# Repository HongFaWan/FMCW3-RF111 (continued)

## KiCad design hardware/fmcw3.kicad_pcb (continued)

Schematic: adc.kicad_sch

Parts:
C19, C20, C217, C218, C222: 1u; SMD_0603
C22, C31, C216, C220: 2.2u; SMD_0603
C23, C24, C25, C27, C30, C219, C221, C223, C224, C225: 100n; SMD_0402
C163, C164, C165, C166, C167, C168: 100p; SMD_0402
C248: 22u; C0805_Murata_GRM21
C249: 47u; C1206_Murata_GRM31
C362: 2.2u; C0603_Assembly_Courtyard_ECO
C400, C401, C410, C412: 100n; SMD_0402; Tolerance 10%; Voltage 50V; MPN GRM155R71H104KE14D; LCSC C77020
C413: 100n; SMD_0402; Voltage 50V; Tolerance 10%; MPN GRM155R71H104KE14D; LCSC C77020
C806: 100n; SMD_0402; MPN GRM155R71H104KE14D
R20, R93: 0; SMD_0402
R21: 33; SMD_0402
R91: 4.7k; SMD_0402
R92: 10k; SMD_0402
R97, R98, R99, R100: 49.9; SMD_0402
R364, R422, R423: 30.9k; R0402_Yageo_Mount_V10; Tolerance 0.1%; MPN RT0402BRD0730K9L; LCSC C852715
R365: 499; R0402_Yageo_Mount_V10
R400, R401, R402, R403, R404, R405, R406, R407, R410, R411, R421, R424, R427, R429: 10k; R0402_Yageo_Mount_V10; Tolerance 0.1%; MPN RT0402BRD0710KL; LCSC C190095
R408, R409: 2.4k; R0402_Yageo_Mount_V10; Tolerance 1%; MPN RC0402FR-072K4L; LCSC C112296
R412: 4.99k; R0402_Yageo_Mount_V10; Tolerance 0.1%; MPN RT0402BRD074K99L; LCSC C852823
R420: 64.9k; R0402_Yageo_Mount_V10; Tolerance 0.1%; MPN RT0402BRD0764K9L; LCSC C852880
R425, R426: 31.6k; R0402_Panasonic_ERA2A_Mount_RF110; Tolerance 0.1%; MPN ERA-2ARB3162X; LCSC C2090771
R428: 100k; R0402_Yageo_Mount_V10; Tolerance 0.1%; MPN RT0402BRD07100KL; LCSC C852472
R431: 20.0k; R0402_Yageo_Mount_V10; Tolerance 0.1%; MPN RT0402BRD0720KL; LCSC C705630
R470: 10; R_0402_UniRoyal_Mount_V17_MFR; Tolerance 1%; MPN 0402WGF100JTCE; LCSC C25077
R807: 10.2k; R_0603_1608Metric; MPN ERA3ARW1022V
R808: 2.21M; R_0603_1608Metric; MPN RC0603FR-072M21L
U8: LTC2292; QFN-64-1EP_9x9mm_Pitch0.5mm
U39: LT3045EMSE#TRPBF; LT3045_MSE12_MFR
U400, U401: TMUX1511PWR; TSSOP-14_4.4x5mm_P0.65mm; MPN TMUX1511PWR; LCSC C2866750
U410: TPS386000RGPR; TPS386000_RGP20_EP2p15; MPN TPS386000RGPR; LCSC C702221
U412: SN74LVC1G17DBVR; SOT-23-5; MPN SN74LVC1G17DBVR; LCSC C7836
U413: SN74LVC1G07DBVR; SOT-23-5; MPN SN74LVC1G07DBVR; LCSC C7829
U806: TLV9021DCKR; SOT-353_SC-70-5; MPN TLV9021DCKR

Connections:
/3V3A: R406.1, R407.1, R425.1; also elsewhere on the board
/3V8: C248.1, U39.1 (IN), U39.2 (IN), U39.3 (IN), U39.4 (EN/UV), U39.7 (PGFB); also elsewhere on the board
/5V: R470.1; also elsewhere on the board
/ADC1+: R100.2; also elsewhere on the board
/ADC1-: R98.2; also elsewhere on the board
/ADC2+: R97.2; also elsewhere on the board
/ADC2-: R99.2; also elsewhere on the board
/ADC_CLK: U8.8 (CLKA), U8.9 (CLKB); also elsewhere on the board
/ADC_VCMA: R406.2, R408.2, R410.1; also elsewhere on the board
/ADC_VCMB: R407.2, R409.2, R411.1; also elsewhere on the board
/fpga/D0: U8.43 (DA0); also elsewhere on the board
/fpga/D1: U8.44 (DA1); also elsewhere on the board
/fpga/D2: U8.45 (DA2); also elsewhere on the board
/fpga/D3: U8.46 (DA3); also elsewhere on the board
/fpga/D4: U8.47 (DA4); also elsewhere on the board
/fpga/D5: U8.48 (DA5); also elsewhere on the board
/fpga/D6: U8.51 (DA6); also elsewhere on the board
/fpga/D7: U8.52 (DA7); also elsewhere on the board
/fpga/D8: U8.53 (DA8); also elsewhere on the board
/fpga/D9: U8.54 (DA9); also elsewhere on the board
/fpga/D10: U8.55 (DA10); also elsewhere on the board
/fpga/D11: U8.56 (DA11); also elsewhere on the board
/fpga/OFA: U8.57 (OFA); also elsewhere on the board
/fpga/OFB: U8.40 (OFB); also elsewhere on the board
/fpga/adc/ADn: C164.2, C165.1, R401.1, U8.2 (AINA-), U400.6 (D2)
/fpga/adc/ADp: C163.2, C164.1, R400.1, U8.1 (AINA+), U400.3 (D1)
/fpga/adc/ANALOG_RAILS_GOOD: R431.2, U410.15 (RESET1_N), U410.16 (RESET2_N), U410.17 (RESET3_N), U410.18 (RESET4_N), U412.2 (A), U806.1 (OUT)
/fpga/adc/ASn: R99.1, U400.5 (S2)
/fpga/adc/ASp: R97.1, U400.2 (S1)
/fpga/adc/BDn: C166.2, C167.1, R402.1, U8.15 (AINB-), U400.8 (D3)
/fpga/adc/BDp: C167.2, C168.1, R403.1, U8.16 (AINB+), U400.11 (D4)
/fpga/adc/BSn: R98.1, U400.9 (S3)
/fpga/adc/BSp: R100.1, U400.12 (S4)
/fpga/adc/GUARD5V_DAMPED: C400.1, C401.1, C410.1, R428.1, R431.1, R470.2, U400.14 (VDD), U401.14 (VDD), U410.1 (MR_N), U410.14 (VDD)
/fpga/adc/ILIM_U39: R365.1, U39.6 (ILIM)
/fpga/adc/MON_5V: R428.2, R429.1, U410.7 (SENSE4L)
/fpga/adc/MON_ADC: R423.2, R424.1, U410.9 (SENSE2)
/fpga/adc/MON_ADC_MID: R422.2, R423.1
/fpga/adc/MON_AMP: R426.2, R427.1, U410.8 (SENSE3)
/fpga/adc/MON_AMP_MID: R425.2, R426.1
/fpga/adc/MON_DIG: R420.2, R421.1, U410.10 (SENSE1)
/fpga/adc/REFHA: C217.1, C220.1, C221.1, U8.3 (REFHA), U8.4 (REFHA)
/fpga/adc/REFHB: C20.1, C22.2, C23.2, U8.13 (REFHB), U8.14 (REFHB)
/fpga/adc/REFLA: C218.1, C220.2, C221.2, U8.5 (REFLA), U8.6 (REFLA)
/fpga/adc/REFLB: C19.1, C22.1, C23.1, U8.11 (REFLB), U8.12 (REFLB)
/fpga/adc/SET_U39: C362.1, R364.1, U39.8 (SET)
/fpga/adc/VCMA_RAW: C216.1, C219.1, R404.1, U8.61 (VCMA), U401.2 (S1)
/fpga/adc/VCMA_SW: R408.1, U401.3 (D1)
/fpga/adc/VCMB_RAW: C30.1, C31.1, R405.1, U8.20 (VCMB), U401.5 (S2)
/fpga/adc/VCMB_SW: R409.1, U401.6 (D2)
ADC3V09: C24.1, C27.1, C222.1, C223.1, C224.1, C249.1, R20.2, R21.2, R91.1, R93.2, R422.1, U8.7 (VDD), U8.10 (VDD), U8.18 (VDD), U8.63 (VDD), U39.10 (OUTS), U39.11 (OUT), U39.12 (OUT); also elsewhere on the board
ADC_DB0: U8.26 (DB0); also elsewhere on the board
ADC_DB1: U8.27 (DB1); also elsewhere on the board
ADC_DB2: U8.28 (DB2); also elsewhere on the board
ADC_DB3: U8.29 (DB3); also elsewhere on the board
ADC_DB4: U8.30 (DB4); also elsewhere on the board
ADC_DB5: U8.33 (DB5); also elsewhere on the board
ADC_DB6: U8.34 (DB6); also elsewhere on the board
ADC_DB7: U8.35 (DB7); also elsewhere on the board
ADC_DB8: U8.36 (DB8); also elsewhere on the board
ADC_DB9: U8.37 (DB9); also elsewhere on the board
ADC_DB10: U8.38 (DB10); also elsewhere on the board
ADC_DB11: U8.39 (DB11); also elsewhere on the board
FMCW_RESET_N: U413.4 (Y); also elsewhere on the board
GND: C19.2, C20.2, C24.2, C25.2, C27.2, C30.2, C31.2, C163.1, C165.2, C166.1, C168.2, C216.2, C217.2, C218.2, C219.2, C222.2, C223.2, C224.2, C225.2, C248.2, C249.2, C362.2, C400.2, C401.2, C410.2, C412.2, C413.2, C806.2, R92.2, R364.2, R365.2, R400.2, R401.2, R402.2, R403.2, R404.2, R405.2, R410.2, R411.2, R412.2, R421.2, R424.2, R427.2, R429.2, R807.2, U8.17 (GND), U8.22 (SHDNB), U8.23 (~OEB), U8.31 (OGND), U8.50 (OGND), U8.58 (~OEA), U8.59 (SHDNA), U8.64 (GND), U8.65 (PAD), U39.9 (GND), U39.13 (GND), U400.7 (GND), U401.7 (GND), U401.8 (D3), U401.9 (S3), U401.10 (SEL3), U401.11 (D4), U401.12 (S4), U401.13 (SEL4), U410.6 (SENSE4H), U410.11 (NC_GND), U410.12 (GND), U410.20 (WDI), U410.21 (EP), U412.3 (GND), U413.3 (GND), U806.2 (V-); also elsewhere on the board
GUARD_ANALOG_EN: R412.1, R808.1, U400.1 (SEL1), U400.4 (SEL2), U400.10 (SEL3), U400.13 (SEL4), U401.1 (SEL1), U401.4 (SEL2), U412.4 (Y), U413.2 (A); also elsewhere on the board
GUARD_REF2V5: U806.4 (-); also elsewhere on the board
MIXER_UV_SENSE: R807.1, R808.2, U806.3 (+); also elsewhere on the board
unnamed: R91.2, R92.1, U8.60 (MODE)
unnamed: R21.1, U8.21 (MUX)
unnamed: R93.1, U8.62 (SENSEA)
unnamed: R20.1, U8.19 (SENSEB)

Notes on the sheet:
2/3 VDD clock duty stabilizer 2s complement signed output This helped for better waveform
Important Note: ECS-TXO-3225MV is pure sin. Adc does not like sin i guess. Other ref designed used clipped more square like sin. That is why clock stabilizer is needed.
U39: OUTS to COUT+; SET/CSET return to COUT-. 499R ILIM; PG/fast start unused.
ANALOG POWER-OFF ISOLATION - WORKING ECO, NOT FOR ORDER
4 IF legs + 2 VCM lines. Original ADC100pF and mandatory reference capacitors remain on ADCside.
GUARD_ANALOG_EN is driven by U410/U411/U412. Digital guards and PCB routing pending.
Guard supply damping: R470 10R / C25077 Only low-current ADC protection and monitor loads. RF power path remains on the original 5V rail.
Local mixer undervoltage interlock

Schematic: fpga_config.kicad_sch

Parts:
C18: 100n; SMD_0402
C170, C171, C187, C189, C190, C191, C192, C193, C197, C198, C199, C200, C201, C202, C203, C204, C250, C251: 470n; SMD_0402
C181: 100u; SMD_1210
C182, C184, C196: 47u; SMD_1206
C183, C185, C186, C188, C194, C195: 4.7u; SMD_0603
C252: 820p; SMD_0402; Manufacturer Part Number GRM1555C1H821GA01D
CON1: SD_Card_DM3BT; DM3BT-DSF-PEJS
D6: LED; Diode_0603
J2: Connector_02x08; PinHeader_2x8_P2.5mm
R10: DNP; SMD_0402; not fitted
R14, R112, R117: 4.7k; SMD_0402
R109: 1k; SMD_0402
R110, R114, R115: 0; SMD_0402
R118: 470; SMD_0402; Manufacturer Part Number RC0402FR-07470RL
R801, R802: 47k; R_0402_1005Metric; Manufacturer Part Number RC0402FR-0747KL
R803: 4.3; R_0402_1005Metric; Manufacturer Part Number RC0402FR-074R3L
SW1, SW2: B3U-1000P; B3U_1000P_MFR
U40: W25Q128JVPIQ; WSON-8_6x5mm_P1p27_W25Q128JVPIQ_WINDOWED; MPN W25Q128JVPIQ; LCSC C190862

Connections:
/1V0: C181.1, C183.1, C184.1, C186.1, C187.1, C189.1, C191.1, C250.1; also elsewhere on the board
/1V8: C182.1, C185.1, C188.1, C190.1, C192.1, C193.1; also elsewhere on the board
/fpga/CARD_DETECT: CON1.9 (CARD_DETECT1); also elsewhere on the board
/fpga/INIT_B: R117.2; also elsewhere on the board
/fpga/M0: R110.2; also elsewhere on the board
/fpga/M1: R114.1; also elsewhere on the board
/fpga/M2: R10.1, R115.1; also elsewhere on the board
/fpga/PIN7: J2.6; also elsewhere on the board
/fpga/PIN8: J2.4; also elsewhere on the board
/fpga/PIN10: J2.5; also elsewhere on the board
/fpga/PIN11: J2.3; also elsewhere on the board
/fpga/PIN12: J2.1; also elsewhere on the board
/fpga/PROG_B: R112.2, SW2.1; also elsewhere on the board
/fpga/SD_CLK: CON1.5 (CLK); also elsewhere on the board
/fpga/SD_CMD: CON1.3 (CMD); also elsewhere on the board
/fpga/SD_DAT0: CON1.7 (DAT0); also elsewhere on the board
/fpga/SD_DAT1: CON1.8 (DAT1); also elsewhere on the board
/fpga/SD_DAT2: CON1.1 (DAT2); also elsewhere on the board
/fpga/SD_DAT3: CON1.2 (CD/DAT3); also elsewhere on the board
/fpga/SPI_CLK: U40.6 (CLK); also elsewhere on the board
/fpga/SPI_CS: R118.2, U40.1 (~CS); also elsewhere on the board
/fpga/SPI_MISO: U40.2 (DO(IO1)); also elsewhere on the board
/fpga/SPI_MOSI: U40.5 (DI(IO0)); also elsewhere on the board
/fpga/USER_LED: R109.1; also elsewhere on the board
/fpga/fpga_config/FLASH_VCC: C252.1, R801.1, R802.2, R803.2, U40.8 (VCC)
FMCW_RESET_N: R14.2, SW1.1; also elsewhere on the board
GND: C18.2, C170.2, C171.2, C181.2, C182.2, C183.2, C184.2, C185.2, C186.2, C187.2, C188.2, C189.2, C190.2, C191.2, C192.2, C193.2, C194.2, C195.2, C196.2, C197.2, C198.2, C199.2, C200.2, C201.2, C202.2, C203.2, C204.2, C250.2, C251.2, C252.2, CON1.6 (VSS), CON1.10 (CARD_DETECT2), CON1.11 (SHELL), D6.1 (K), J2.14, J2.16, R114.2, R115.2, SW1.2, SW2.2, U40.4 (GND), U40.9 (EP); also elsewhere on the board
LO_ADC_CONV_REQ_N: J2.7; also elsewhere on the board
LO_ADC_CS_N: J2.9; also elsewhere on the board
LO_ADC_SCK: J2.8; also elsewhere on the board
LO_ADC_SDO: J2.10; also elsewhere on the board
LO_DSA_LE: J2.2; also elsewhere on the board
unnamed: D6.2 (A), R109.2
unnamed: R802.1, U40.7 (~HOLD(IO3))
unnamed: R801.2, U40.3 (~WP(IO2))
PA_ARM_PULSE: J2.11; also elsewhere on the board
PA_INTERLOCK_N: J2.12; also elsewhere on the board

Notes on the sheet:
VCCBRAM
in SPI Flash mode, JTAG can be used.
VCCINT
32 is not supported by vivado openFPGALoader is needed. 128 is same price supported and more memory is available.
VCCAUX
VCCO_0
Mode M[2:0] Master SPI 001 JTAG 101
VCCO

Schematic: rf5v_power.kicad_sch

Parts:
C657: 2.2uF effective at DC, ≥50V; C_1210_3225Metric; Manufacturer Part Number C1210C106K5RAC7800
C658: 100nF ≥50V; C_0603_1608Metric; Manufacturer Part Number C0603C104K5RACTU
C659: 1uF; C_0603_1608Metric; Manufacturer Part Number C0603C105K4RACTU
C660, C661, C662: C3225X7R1E226M250AB; C_1210_3225Metric; Manufacturer Part Number C3225X7R1E226M250AB
C663, C665, C666: C2012X5R1E226M125AC; C_0805_2012Metric; Manufacturer Part Number C2012X5R1E226M125AC
C664: 470nF ≥16V; C_0603_1608Metric; Manufacturer Part Number C0603C474K4RACTU
R661: 47.5k, 0.1%; R_0402_1005Metric; Manufacturer Part Number RT0402BRD0747K5L
R662: 10k, 0.1%; R_0402_1005Metric; Manufacturer Part Number RT0402BRD0710KL
R664: 49.9k, 0.1%; R_0402_1005Metric; Manufacturer Part Number RT0402BRD0749K9L
U657: TPSM365R6FRDNR; TPSM365R6_RDN0011A_TI_4mil; Manufacturer Part Number TPSM365R6FRDNR
U658: LT3045EMSE#TRPBF; LT3045_MSE12_MFR; Manufacturer Part Number LT3045EMSE#TRPBF

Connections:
/power/12V: C657.1, C658.1, U657.2 (EN), U657.3 (VIN); also elsewhere on the board
/power/RF5V power/LO_BUCK_FB: R661.2, R662.1, U657.9 (FB)
/power/RF5V power/LO_BUCK_VCC: C659.1, U657.8 (VCC), U657.11 (RT)
/power/RF5V power/LO_LDO_SET: C664.1, R664.1, U658.8 (SET)
GND: C657.2, C658.2, C659.2, C660.2, C661.2, C662.2, C663.2, C664.2, C665.2, C666.2, R662.2, R664.2, U657.10 (PGND), U658.6 (ILIM), U658.9 (GND), U658.13 (EP); also elsewhere on the board
LO5V75: C660.1, C661.1, C662.1, C663.1, R661.1, U657.4 (VOUT), U658.1 (IN1), U658.2 (IN2), U658.3 (IN3), U658.4 (EN/UV), U658.7 (PGFB); also elsewhere on the board
RF5V_NEW: C665.1, C666.1, U658.10 (OUTS), U658.11 (OUT1), U658.12 (OUT2); also elsewhere on the board

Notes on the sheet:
Independent LO power supply

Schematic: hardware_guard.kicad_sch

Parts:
C650, C651, C652, C653, C654, C655, C656: 100nF; C_0402_1005Metric; Manufacturer Part Number GRM155R71H104KE14D
C670, C671, C673, C674: 100n; C_0402_1005Metric; Manufacturer Part Number GRM155R71H104KE14D
C672: 1u; C_0603_1608Metric; Manufacturer Part Number C0603C105K4RACTU
Q650: MMBT3904LT1G; SOT-23; Manufacturer Part Number MMBT3904LT1G
Q651: AO3400A; SOT-23; Manufacturer Part Number AO3400A
R650: 73.2k, 0.1%,25ppm; R_0402_1005Metric; Manufacturer Part Number RT0402BRD0773K2L
R651, R653: 10k, 0.1%,25ppm; R_0402_1005Metric; Manufacturer Part Number RT0402BRD0710KL
R652: 110k, 0.1%,25ppm; R_0402_1005Metric; Manufacturer Part Number RT0402BRD07110KL
R654, R655, R656, R657, R679, R680: 47k; R_0402_1005Metric; Manufacturer Part Number RC0402FR-0747KL
R658: 1.50k; R_0402_1005Metric; Manufacturer Part Number RC0402FR-071K5L
R659: 68; R_0402_1005Metric; Manufacturer Part Number RC0402FR-0768RL
R660, R674, R678: 4.7k; R_0402_1005Metric; Manufacturer Part Number RC0402FR-074K7L
R670: 2.00k 0.1% 25ppm; R_0402_1005Metric; Manufacturer Part Number RT0402BRD072KL
R671: 2.15k 0.1% 25ppm; R_0402_1005Metric; Manufacturer Part Number RT0402BRD072K15L
R672: 24 1% 100ppm; R_0402_1005Metric; Manufacturer Part Number RC0402FR-0724RL
R673: 560k 1% 100ppm; R_0402_1005Metric; Manufacturer Part Number RC0402FR-07560KL
R675: 13.0k 0.1% 25ppm; R_0402_1005Metric; Manufacturer Part Number RT0402BRD0713KL
R676: 11.0k 0.1% 25ppm; R_0402_1005Metric; Manufacturer Part Number RT0402BRD0711KL
R677: 3.3M; R_0402_1005Metric; Manufacturer Part Number RC0402FR-073M3L
U650, U651: TLV3012BIDBVR; SOT-23-6; Manufacturer Part Number TLV3012BIDBVR
U652: SN74LVC2G08DCUR; VSSOP-8_2.3x2mm_P0.5mm; Manufacturer Part Number SN74LVC2G08DCUR
U653: SN74LVC2G07DCKR; SOT-363_SC-70-6; Manufacturer Part Number SN74LVC2G07DCKR
U654, U655: SN74LVC1G11DCKR; SOT-363_SC-70-6; Manufacturer Part Number SN74LVC1G11DCKR
U656: SN74LVC1G74DCUR; VSSOP-8_2.3x2mm_P0.5mm; Manufacturer Part Number SN74LVC1G74DCUR
U667: TLV9022DDFR; SOT-23-8; Manufacturer Part Number TLV9022DDFR
U668: REF3425IDBVR; SOT-23-6; Manufacturer Part Number REF3425IDBVR
U669: SN74LVC1G11DBVR; SOT-23-6; Manufacturer Part Number SN74LVC1G11DBVR
U670: SN74LVC1G97DBVR; SOT-23-6; Manufacturer Part Number SN74LVC1G97DBVR

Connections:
/power/Rail interlock/ARM_Q: U652.6 (2B), U656.5 (Q)
/power/Rail interlock/GUARD_ARMED: U652.3 (2Y), U655.3 (B)
/power/Rail interlock/LO5V75_OK: R677.1, R678.2, U667.7 (PRE_OD), U669.6 (C)
/power/Rail interlock/LO5V75_UV_SENSE: R675.2, R676.1, R677.2, U667.5 (IN2+)
/power/Rail interlock/OV_REF: U651.3 (IN+), U651.5 (REF)
/power/Rail interlock/PA_KILL_BASE: Q650.1 (B), Q651.3 (D), R658.2
/power/Rail interlock/PA_KILL_RELEASE: Q651.1 (G), R659.2, R660.1
/power/Rail interlock/PA_LATCH_CLR_N: U654.4 (Y), U656.6 (NCLR)
/power/Rail interlock/RAW_OV_OK: U651.1 (OUT), U652.2 (1B)
/power/Rail interlock/RAW_OV_SENSE: R652.2, R653.1, U651.4 (IN-)
/power/Rail interlock/RAW_UV_OK: U650.1 (OUT), U652.1 (1A)
/power/Rail interlock/RAW_UV_SENSE: R650.2, R651.1, U650.3 (IN+)
/power/Rail interlock/RF5_LEVEL_OK: R673.1, R674.2, U667.1 (RF5_OD), U669.3 (B)
/power/Rail interlock/RF5_UV_LOW: R671.2, R672.1
/power/Rail interlock/RF5_UV_SENSE: R670.2, R671.1, R673.2, U667.3 (IN1+)
/power/Rail interlock/UV_REF: U650.4 (IN-), U650.5 (REF)
FMCW_RESET_N: U653.6 (1Y_OD), U654.3 (B); also elsewhere on the board
FTDI_RESET_N: U653.4 (2Y_OD); also elsewhere on the board
GND: C650.2, C651.2, C652.2, C653.2, C654.2, C655.2, C656.2, C670.2, C671.2, C672.2, C673.2, C674.2, Q650.2 (E), Q651.2 (S), R651.2, R653.2, R654.2, R655.2, R656.2, R657.2, R660.2, R672.2, R676.2, R679.2, U650.2 (V-), U651.2 (V-), U652.4 (GND), U653.2 (GND), U654.2 (GND), U655.2 (GND), U656.4 (GND), U667.4 (GND), U668.1 (GND), U668.2 (GND), U669.2 (GND), U670.2 (GND); also elsewhere on the board
GUARD_ANALOG_EN: U652.5 (2A); also elsewhere on the board
GUARD_EXISTING_RF_OK: U669.4 (Y); also elsewhere on the board
GUARD_RAW_OK: R654.1, U652.7 (1Y), U669.1 (A); also elsewhere on the board
GUARD_REF2V5: C672.1, U667.2 (IN1-), U667.6 (IN2-), U668.5 (OUT_S), U668.6 (REF); also elsewhere on the board
GUARD_RF_READY: R679.1, U653.1 (1A), U654.1 (A), U655.1 (A), U670.6 (SEL); also elsewhere on the board
GUARD_USB_READY: U653.3 (2A); also elsewhere on the board
LO5V75: R675.1; also elsewhere on the board
LO_ADC_CONV: U670.4 (Y); also elsewhere on the board
LO_ADC_CONV_REQ_N: R680.2, U670.3 (DATA_VALID); also elsewhere on the board
PA_ARM_PULSE: R655.1, U656.1 (CLK); also elsewhere on the board
PA_EN_G: Q650.3 (C); also elsewhere on the board
PA_INTERLOCK_N: R656.1, U654.6 (C), U655.6 (C); also elsewhere on the board
PA_OE_HW: R657.1, R659.1, U655.4 (Y); also elsewhere on the board
PA_VCC1: R658.1; also elsewhere on the board
RF5V_NEW: R670.1; also elsewhere on the board
VIN_RAW_12V: R650.1, R652.1; also elsewhere on the board

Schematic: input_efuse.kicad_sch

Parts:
C680: 100nF 100V; C_0805_2012Metric
C681: 2.2uF 100V X7R; C_1210_3225Metric
C682: 22nF 50V; C_0603_1608Metric
C683: EEH-ZK1V101XP; CP_Elec_6.3x7.7
R780: 64.9k 0.1%; R_0603_1608Metric
R781, R783: 10.0k 0.1%; R_0603_1608Metric
R782: 121k 0.1%; R_0603_1608Metric
R784: 5.49k 0.1%; R_0603_1608Metric
R785: 1.2R pulse rated; R_1210_3225Metric
U680: TPS26600PWPR; HTSSOP-16-1EP_4.4x5mm_P0.65mm_EP3.4x5mm_Mask2.66x2.46mm

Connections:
/power/12V: C683.1; also elsewhere on the board
/power/Input eFuse/DAMP: C681.1, R785.2
/power/Input eFuse/DVDT: C682.1, U680.12 (dVdT)
/power/Input eFuse/EFUSE_RTN: C682.2, R781.2, R783.2, R784.2, U680.6 (MODE), U680.8 (RTN), U680.17 (RTN)
/power/Input eFuse/ILIM: R784.1, U680.11 (ILIM)
/power/Input eFuse/OV: R782.2, R783.1, U680.5 (OVP)
/power/Input eFuse/UV: R780.2, R781.1, U680.3 (UVLO)
EFUSE_OUT_12V: U680.15 (OUT), U680.16 (OUT); also elsewhere on the board
GND: C680.2, C681.2, C683.2, U680.9 (GND); also elsewhere on the board
VIN_RAW_12V: C680.1, R780.1, R782.1, R785.1, U680.1 (IN), U680.2 (IN); also elsewhere on the board

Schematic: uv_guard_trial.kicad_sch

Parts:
C790, C791, C792, C793: 100n; C_0402_1005Metric; Manufacturer Part Number GRM155R71H104KE14D
C794: 33p C0G; C_0402_1005Metric; Manufacturer Part Number CC0402FRNPO9BN330
R790: 4.30k 0.05% 10ppm; R_0402_1005Metric; Manufacturer Part Number ERA2VRW4301X
R791: 1.50k 0.05% 10ppm; R_0402_1005Metric; Manufacturer Part Number ERA2VRW1501X
R792: 2.61k 0.1% 10ppm; R_0402_1005Metric; Manufacturer Part Number ERA-2ARB2611X
R793: 10.0k 0.1% 10ppm; R_0402_1005Metric; Manufacturer Part Number ERA-2ARB103X
R794, R795: 4.7k; R_0402_1005Metric; Manufacturer Part Number RC0402FR-074K7L
R796: 10k; R_0402_1005Metric; Manufacturer Part Number RC0402FR-0710KL
R797: 47k; R_0402_1005Metric; Manufacturer Part Number RC0402FR-0747KL
U685: TLV9022DDFR; SOT-23-8; Manufacturer Part Number TLV9022DDFR
U686, U687: SN74LVC1G11DCKR; SOT-363_SC-70-6; Manufacturer Part Number SN74LVC1G11DCKR
U688: TPS3808G33DBVR; SOT-23-6; Manufacturer Part Number TPS3808G33DBVR

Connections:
/power/Tune and IO protection/IO_FAST_OK: R795.2, U685.7 (IO_OD), U687.3 (B), U688.3 (MR)
/power/Tune and IO protection/IO_STARTUP_OK: R796.2, U687.6 (C), U688.1 (RESET_OD)
/power/Tune and IO protection/IO_UV_SENSE: R792.2, R793.1, U685.5 (IN2+)
/power/Tune and IO protection/TUNE_OK: R794.2, U685.1 (TUNE_OD), U686.3 (B)
/power/Tune and IO protection/TUNE_UV_SENSE: C794.1, R790.2, R791.1, U685.3 (IN1+)
GND: C790.2, C791.2, C792.2, C793.2, C794.2, R791.2, R793.2, R797.2, U685.4 (GND), U686.2 (GND), U687.2 (GND), U688.2 (GND); also elsewhere on the board
GUARD_EXISTING_RF_OK: U686.1 (A); also elsewhere on the board
GUARD_RAW_OK: U687.1 (A); also elsewhere on the board
GUARD_REF2V5: U685.2 (IN1-), U685.6 (IN2-); also elsewhere on the board
GUARD_RF_READY: U686.4 (Y); also elsewhere on the board
GUARD_USB_READY: R797.1, U686.6 (C), U687.4 (Y); also elsewhere on the board
TUNE_10V: R790.1; also elsewhere on the board

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
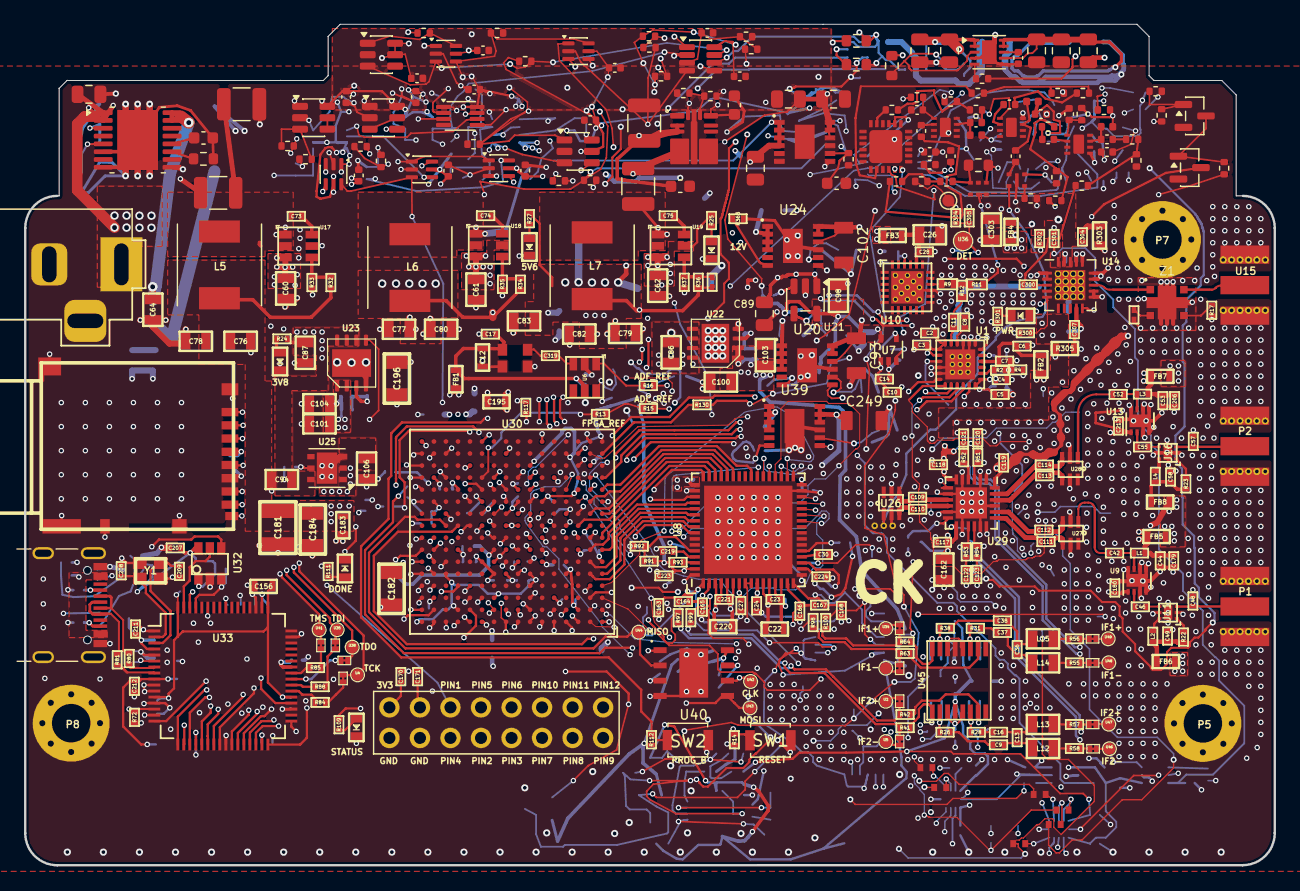
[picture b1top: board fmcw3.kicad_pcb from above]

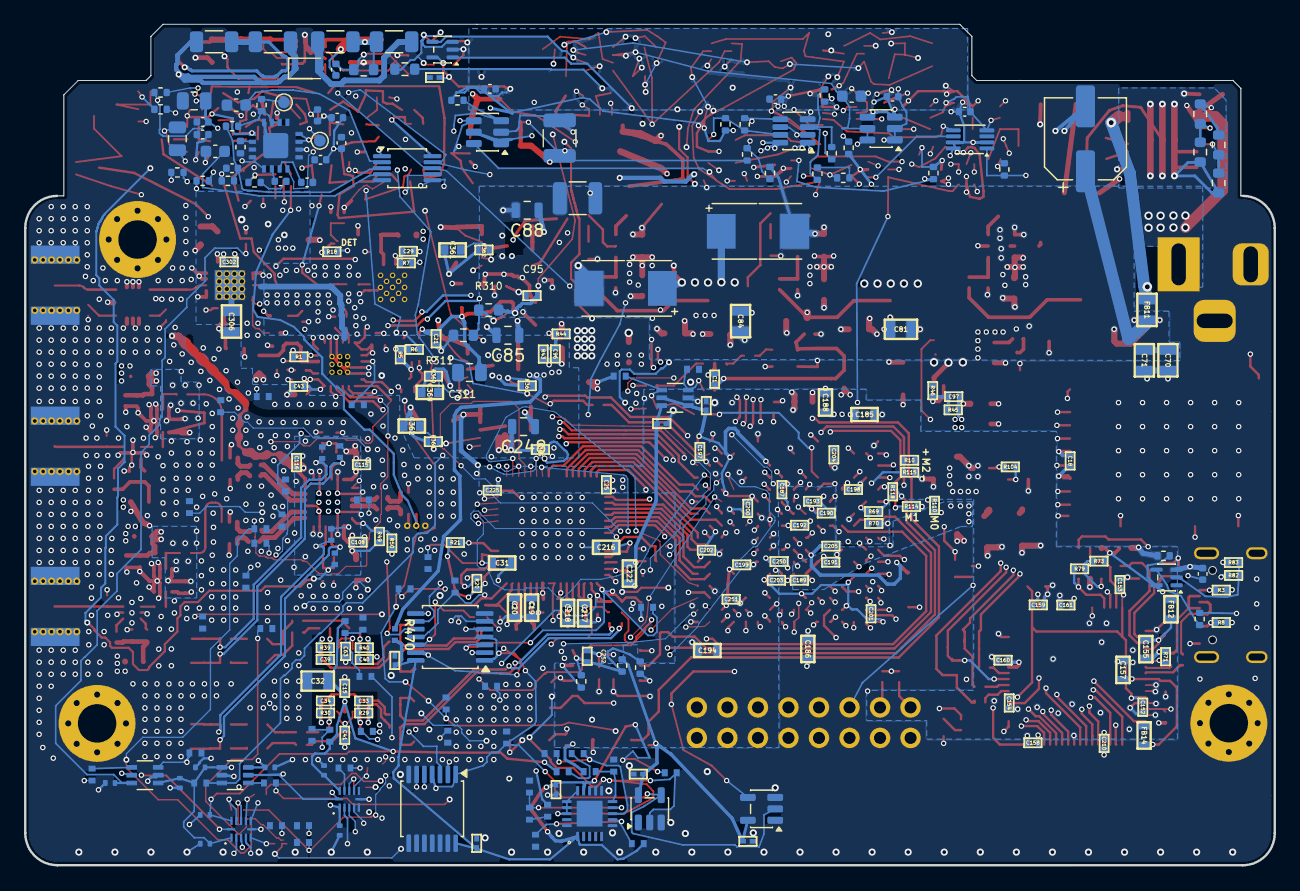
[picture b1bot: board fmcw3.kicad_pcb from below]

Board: 6 copper layers, 104.0 x 70.0 mm, 662 parts (265 on the bottom side), 393 nets.

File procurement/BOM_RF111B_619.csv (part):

位号,单片实装净数,面,原理图标值,工程封装,设计订货号,制造商,型号选择记录,工程及来料要求,核对链接
C1,1,底,100n,Footprints:SMD_0402,GRM155R71H104KE14D,Murata,工程原指定,Tolerance: 10%; Voltage: 50V,
C2,1,顶,100n,Footprints:SMD_0402,GRM155R71H104KE14D,Murata,工程原指定,Tolerance: 10%; Voltage: 50V,
C3,1,顶,10p,Footprints:SMD_0402,GRM1555C1H100GA01D,muRata,工程原指定,,
C4,1,顶,100n,Footprints:SMD_0402,GRM155R71H104KE14D,Murata,工程原指定,Tolerance: 10%; Voltage: 50V,
C5,1,顶,10p,Footprints:SMD_0402,GRM1555C1H100GA01D,muRata,工程原指定,,
C6,1,顶,100n,Footprints:SMD_0402,GRM155R71H104KE14D,Murata,工程原指定,Tolerance: 10%; Voltage: 50V,
C7,1,顶,10p,Footprints:SMD_0402,GRM1555C1H100GA01D,muRata,工程原指定,,
C8,1,顶,10p,Footprints:SMD_0402,GRM1555C1H100GA01D,muRata,工程原指定,,
C9,1,顶,10n,Footprints:SMD_0402,GRM1555C1E103GE01D,Murata,工程原指定,,
C10,1,顶,6.8n,Footprints:SMD_0402,GRM1555C1H682GE01D,muRata,工程原指定,,
C11,1,顶,10p,Footprints:SMD_0402,GRM1555C1H100GA01D,muRata,工程原指定,,
C12,1,顶,1u,Footprints:SMD_0603,GRM188R61E105KA12D,muRata,工程原指定,,
C13,1,顶,2.2n,Footprints:SMD_0402,GRM1555C1H222GA01D,muRata,工程原指定,,
C14,1,顶,68p,Footprints:SMD_0402,GRM1555C1H680GA01D,muRata,工程原指定,,
C15,1,底,100n,Footprints:SMD_0402,GRM155R71H104KE14D,Murata,工程原指定,Tolerance: 10%; Voltage: 50V,
C16,1,顶,10n,Footprints:SMD_0402,GRM1555C1E103GE01D,Murata,工程原指定,,
C17,1,顶,100n,Footprints:SMD_0402,GRM155R71H104KE14D,Murata,工程原指定,Tolerance: 10%; Voltage: 50V,
C18,1,底,100n,Footprints:SMD_0402,GRM155R71H104KE14D,Murata,工程原指定,Tolerance: 10%; Voltage: 50V,
C19,1,底,1u,Footprints:SMD_0603,GRM188R61E105KA12D,muRata,工程原指定,,
C20,1,底,1u,Footprints:SMD_0603,GRM188R61E105KA12D,muRata,工程原指定,,
C21,1,底,100n,Footprints:SMD_0402,GRM155R71H104KE14D,Murata,工程原指定,Tolerance: 10%; Voltage: 50V,
C22,1,顶,2.2u,Footprints:SMD_0603,GRM188R61A225KE34D,muRata,工程原指定,,
C23,1,顶,100n,Footprints:SMD_0402,GRM155R71H104KE14D,Murata,工程原指定,Tolerance: 10%; Voltage: 50V,
C24,1,顶,100n,Footprints:SMD_0402,GRM155R71H104KE14D,Murata,工程原指定,Tolerance: 10%; Voltage: 50V,
C25,1,底,100n,Footprints:SMD_0402,GRM155R71H104KE14D,Murata,工程原指定,Tolerance: 10%; Voltage: 50V,
C26,1,顶,10u,Footprints:SMD_0805,GRM21BR61E106KA73L,muRata,工程原指定,,
C27,1,顶,100n,Footprints:SMD_0402,GRM155R71H104KE14D,Murata,工程原指定,Tolerance: 10%; Voltage: 50V,
C28,1,顶,10n,Footprints:SMD_0402,GRM1555C1E103GE01D,Murata,工程原指定,,
C30,1,顶,100n,Footprints:SMD_0402,GRM155R71H104KE14D,Murata,工程原指定,Tolerance: 10%; Voltage: 50V,
C31,1,底,2.2u,Footprints:SMD_0603,GRM188R61A225KE34D,muRata,工程原指定,,
C33,1,底,5p,Footprints:SMD_0402,GRM1555C1H5R0BA01D,muRata,工程原指定,,
C34,1,底,5p,Footprints:SMD_0402,GRM1555C1H5R0BA01D,muRata,工程原指定,,
C36,1,顶,2.2n,Footprints:SMD_0402,GRM1555C1H222GA01D,muRata,工程原指定,,
C37,1,顶,10n,Footprints:SMD_0402,GRM1555C1E103GE01D,Murata,工程原指定,,
C38,1,顶,10n,Footprints:SMD_0402,GRM1555C1E103GE01D,Murata,工程原指定,,
C39,1,底,5p,Footprints:SMD_0402,GRM1555C1H5R0BA01D,muRata,工程原指定,,
C40,1,底,5p,Footprints:SMD_0402,GRM1555C1H5R0BA01D,muRata,工程原指定,,
C41,1,底,100n,Footprints:SMD_0402,GRM155R71H104KE14D,Murata,工程原指定,Tolerance: 10%; Voltage: 50V,
C42,1,顶,18p,Footprints:SMD_0402,GRM1555C1H180JA01D,muRata,工程原指定,,
C43,1,底,100n,Footprints:SMD_0402,GRM155R71H104KE14D,Murata,工程原指定,Tolerance: 10%; Voltage: 50V,
C44,1,顶,10p,Footprints:SMD_0402,GRM1555C1H100GA01D,muRata,工程原指定,,
C46,1,顶,18p,Footprints:SMD_0402,GRM1555C1H180JA01D,muRata,工程原指定,,
C48,1,顶,0.5p,Footprints:SMD_0402,GRM1555C1HR50WA01D,muRata,工程原指定,,
C49,1,顶,100n,Footprints:SMD_0402,GRM155R71H104KE14D,Murata,工程原指定,Tolerance: 10%; Voltage: 50V,
C52,1,顶,18p,Footprints:SMD_0402,GRM1555C1H180JA01D,muRata,工程原指定,,
C53,1,顶,10p,Footprints:SMD_0402,GRM1555C1H100GA01D,muRata,工程原指定,,
C55,1,顶,18p,Footprints:SMD_0402,GRM1555C1H180JA01D,muRata,工程原指定,,
C57,1,顶,0.5p,Footprints:SMD_0402,GRM1555C1HR50WA01D,muRata,工程原指定,,
C58,1,顶,100n,Footprints:SMD_0402,GRM155R71H104KE14D,Murata,工程原指定,Tolerance: 10%; Voltage: 50V,
C60,1,顶,10u,Footprints:SMD_0805,GRM21BR61E106KA73L,muRata,工程原指定,,
C61,1,顶,10u,Footprints:SMD_0805,GRM21BR61E106KA73L,muRata,工程原指定,,
C62,1,顶,10u,Footprints:SMD_0805,GRM21BR61E106KA73L,muRata,工程原指定,,
C63,1,底,100n,Footprints:SMD_0402,GRM155R71H104KE14D,Murata,工程原指定,Tolerance: 10%; Voltage: 50V,
C64,1,顶,10u,Footprints:SMD_0805,GRM21BR61E106KA73L,muRata,工程原指定,,
C70,1,底,10u,Footprints:SMD_0805,GRM21BR61E106KA73L,muRata,工程原指定,,
C71,1,底,10u,Footprints:SMD_0805,GRM21BR61E106KA73L,muRata,工程原指定,,
C73,1,顶,100n,Footprints:SMD_0402,GRM155R71H104KE14D,Murata,工程原指定,Tolerance: 10%; Voltage: 50V,
C74,1,顶,100n,Footprints:SMD_0402,GRM155R71H104KE14D,Murata,工程原指定,Tolerance: 10%; Voltage: 50V,
C75,1,顶,100n,Footprints:SMD_0402,GRM155R71H104KE14D,Murata,工程原指定,Tolerance: 10%; Voltage: 50V,
C76,1,顶,10u,Footprints:SMD_0805,GRM21BR61E106KA73L,muRata,工程原指定,,
C77,1,顶,10u,Footprints:SMD_0805,GRM21BR61E106KA73L,muRata,工程原指定,,
C78,1,顶,10u,Footprints:SMD_0805,GRM21BR61E106KA73L,muRata,工程原指定,,
C79,1,顶,10u,Footprints:SMD_0805,GRM21BR61E106KA73L,muRata,工程原指定,,
C80,1,顶,10u,Footprints:SMD_0805,GRM21BR61E106KA73L,muRata,工程原指定,,
C81,1,底,10u,Footprints:SMD_0805,GRM21BR61E106KA73L,muRata,工程原指定,,
C82,1,顶,10u,Footprints:SMD_0805,GRM21BR61E106KA73L,muRata,工程原指定,,
C83,1,顶,10u,Footprints:SMD_0805,GRM21BR61E106KA73L,muRata,工程原指定,,
C84,1,底,10u,Footprints:SMD_0805,GRM21BR61E106KA73L,muRata,工程原指定,,
C85,1,底,22u,ECO_PWR:C0805_Murata_GRM21,GRM21BR61E226ME44L,muRata,工程原指定,,
C86,1,顶,10u,Footprints:SMD_0805,GRM21BR61E106KA73L,muRata,工程原指定,,
C87,1,顶,10u,Footprints:SMD_0805,GRM21BR61E106KA73L,muRata,工程原指定,,
C88,1,底,22u,ECO_PWR:C0805_Murata_GRM21,GRM21BR61E226ME44L,muRata,工程原指定,,
C89,1,顶,22u,fmcw3:C0805_ECO,GRM21BR61E226ME44L,muRata,工程原指定,,
C93,1,顶,47u,ECO_PWR:C1206_Murata_GRM31,GRM31CR61A476KE15L,muRata,工程原指定,,
C94,1,顶,10u,Footprints:SMD_0805,GRM21BR61E106KA73L,muRata,工程原指定,,
C95,1,底,10n,Footprints:SMD_0402,GRM1555C1E103GE01D,Murata,工程原指定,,
C96,1,底,470n,Footprints:SMD_0402,GRM155R61A474KE15D,muRata,工程原指定,,
C97,1,底,470n,Footprints:SMD_0402,GRM155R61A474KE15D,muRata,工程原指定,,
C98,1,顶,22u,Footprints:SMD_0805,GRM21BR61E226ME44L,muRata,工程原指定,,
C100,1,顶,10u,Footprints:SMD_0805,GRM21BR61E106KA73L,muRata,工程原指定,,
C101,1,顶,10u,Footprints:SMD_0805,GRM21BR61E106KA73L,muRata,工程原指定,,
C102,1,顶,47u,ECO_PWR:C1206_Murata_GRM31,GRM31CR61A476KE15L,muRata,工程原指定,,
C106,1,顶,10u,Footprints:SMD_0805,GRM21BR61E106KA73L,muRata,工程原指定,,
C108,1,底,100n,Footprints:SMD_0402,GRM155R71H104KE14D,Murata,工程原指定,Tolerance: 10%; Voltage: 50V,
C109,1,顶,3p,Footprints:SMD_0402,GJM1555C1H3R0BB01D,Murata,工程原指定,Tolerance: +/-0.1pF; Voltage: 50V,
C110,1,顶,3p,Footprints:SMD_0402,GJM1555C1H3R0BB01D,Murata,工程原指定,Tolerance: +/-0.1pF; Voltage: 50V,
C111,1,顶,3p,Footprints:SMD_0402,GJM1555C1H3R0BB01D,Murata,工程原指定,Tolerance: +/-0.1pF; Voltage: 50V,
C112,1,顶,3p,Footprints:SMD_0402,GJM1555C1H3R0BB01D,Murata,工程原指定,Tolerance: +/-0.1pF; Voltage: 50V,
C113,1,顶,3p,Footprints:SMD_0402,GJM1555C1H3R0BB01D,Murata,工程原指定,Tolerance: +/-0.1pF; Voltage: 50V,
C114,1,顶,3p,Footprints:SMD_0402,GJM1555C1H3R0BB01D,Murata,工程原指定,Tolerance: +/-0.1pF; Voltage: 50V,
C115,1,底,100n,Footprints:SMD_0402,GRM155R71H104KE14D,Murata,工程原指定,Tolerance: 10%; Voltage: 50V,
C116,1,底,100n,Footprints:SMD_0402,GRM155R71H104KE14D,Murata,工程原指定,Tolerance: 10%; Voltage: 50V,
C117,1,顶,100p,Footprints:SMD_0402,GRM1555C1H101JA01D,muRata,工程原指定,,
C118,1,顶,100p,Footprints:SMD_0402,GRM1555C1H101JA01D,muRata,工程原指定,,
C119,1,顶,100p,Footprints:SMD_0402,GRM1555C1H101JA01D,muRata,工程原指定,,
C120,1,顶,100n,Footprints:SMD_0402,GRM155R71H104KE14D,Murata,工程原指定,Tolerance: 10%; Voltage: 50V,
C121,1,顶,100n,Footprints:SMD_0402,GRM155R71H104KE14D,Murata,工程原指定,Tolerance: 10%; Voltage: 50V,
C122,1,顶,100n,Footprints:SMD_0402,GRM155R71H104KE14D,Murata,工程原指定,Tolerance: 10%; Voltage: 50V,
C123,1,顶,100n,Footprints:SMD_0402,GRM155R71H104KE14D,Murata,工程原指定,Tolerance: 10%; Voltage: 50V,
C152,1,底,100n,Footprints:SMD_0402,GRM155R71H104KE14D,Murata,工程原指定,Tolerance: 10%; Voltage: 50V,
C153,1,底,100n,Footprints:SMD_0402,GRM155R71H104KE14D,Murata,工程原指定,Tolerance: 10%; Voltage: 50V,
C154,1,底,100n,Footprints:SMD_0402,GRM155R71H104KE14D,Murata,工程原指定,Tolerance: 10%; Voltage: 50V,
C155,1,底,4.7u,Footprints:SMD_0603,GRM188R61A475KE15D,muRata,工程原指定,,
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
